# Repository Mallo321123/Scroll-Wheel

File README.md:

# 🖱️ High-Resolution Scroll Wheel

> A large, high-resolution scroll wheel inspired by [Engineer Bo](https://www.patreon.com/c/engineerbo/posts)'s [YouTube video](https://www.youtube.com/watch?v=FSy9G6bNuKA).

---

## [Documentation](https://wiki.mariolanghammer.de/en/Projects/Scroll-Wheel)

---

> ⚠️ **Early Development Phase**  
> This project is still under development. Use at your own risk.

---

## 📅 Roadmap

- [X] BLE HID Support
- [ ] Mouse Wheel Click Functionality
- [ ] Automatic power off
- [ ] Battery Level tuning
- [ ] Enclosure refinements
- [ ] Scroll acceleration modes

---

## 🔧 Hardware Overview

- **Main Controller:** ESP32 (subject to maybe change later)
- **Magnetic Encoder:** [AS5600](https://ams-osram.com/products/sensor-solutions/position-sensors/ams-as5600-position-sensor)
- **Battery Pack:** S3P2 NiMH Eneloop cells

---

## 💻 Software Architecture

The entire functionality is now handled by a single **ESP32 microcontroller** using **BLE HID** (Human Interface Device) mode.

- The scroll wheel inputs are directly interpreted by the ESP32.
- Input data (e.g. rotation) is sent over **Bluetooth Low Energy** as **HID events**, emulating a native scroll device.
- No additional driver or software is needed on the PC — it works like a standard Bluetooth mouse/scroll input.

> ✅ This simplifies the setup significantly and increases compatibility across Linux, Windows, and macOS.

---

## 🧩 Required Components

| Part                             | Quantity |
|----------------------------------|----------|
| Main PCB (pre-soldered)          | 1        |
| Bearing (65×85×10 mm)            | 1        |
| JST GH Cable Kit                 | 1 set    |
| Cylinder Magnets (3×12 mm)       | 7        |
| 3D-Printed Parts                 | 3        |
| S3P2 NiMH Battery Pack           | 1        |
| M2×5 Screws                      | 5        |

---

## 🛠️ Build Guide

### 🔄 Bearing Preparation

Factory bearings may feel stiff due to thick grease. Here's how to optimize smoothness:

1. Remove both sealing rings.
2. Soak the bearing in **isopropyl alcohol** (or another grease remover).
3. Scrub out all remaining grease.
4. Let it dry for ~3 hours.
5. Reinstall **one** sealing ring.
6. Add **light machine oil** generously into the bearing.
7. Reinstall the **second** sealing ring.
8. Spin the bearing multiple times to distribute the oil.
9. *(Optional)* Remove the seals again for an even smoother feel (at the cost of dust protection).

---

## 🚧 Development Gallery

### 🔌 First PCB Prototype (with known bugs)

---

### 🧱 PCB Inside the Case

---

### 🧪 First Firmware Test (External ESP32)

---

### 🧰 Fully Assembled PCB

---

### 🆕 PCB V2 – Improved & Debugged

---

## 🤝 Contributing

Pull requests, suggestions, and feedback are always welcome — feel free to get involved and help improve the project!  
Prototyping and hardware development can get expensive quickly, so if you’d like to support the project financially:

&nbsp;

Every bit helps keep the ideas (and soldering irons) running!

## Credits
Credits to [T-vk](https://github.com/T-vK) for creating the [ESP32 BLE Mouse](https://github.com/T-vK/ESP32-BLE-Mouse) Library

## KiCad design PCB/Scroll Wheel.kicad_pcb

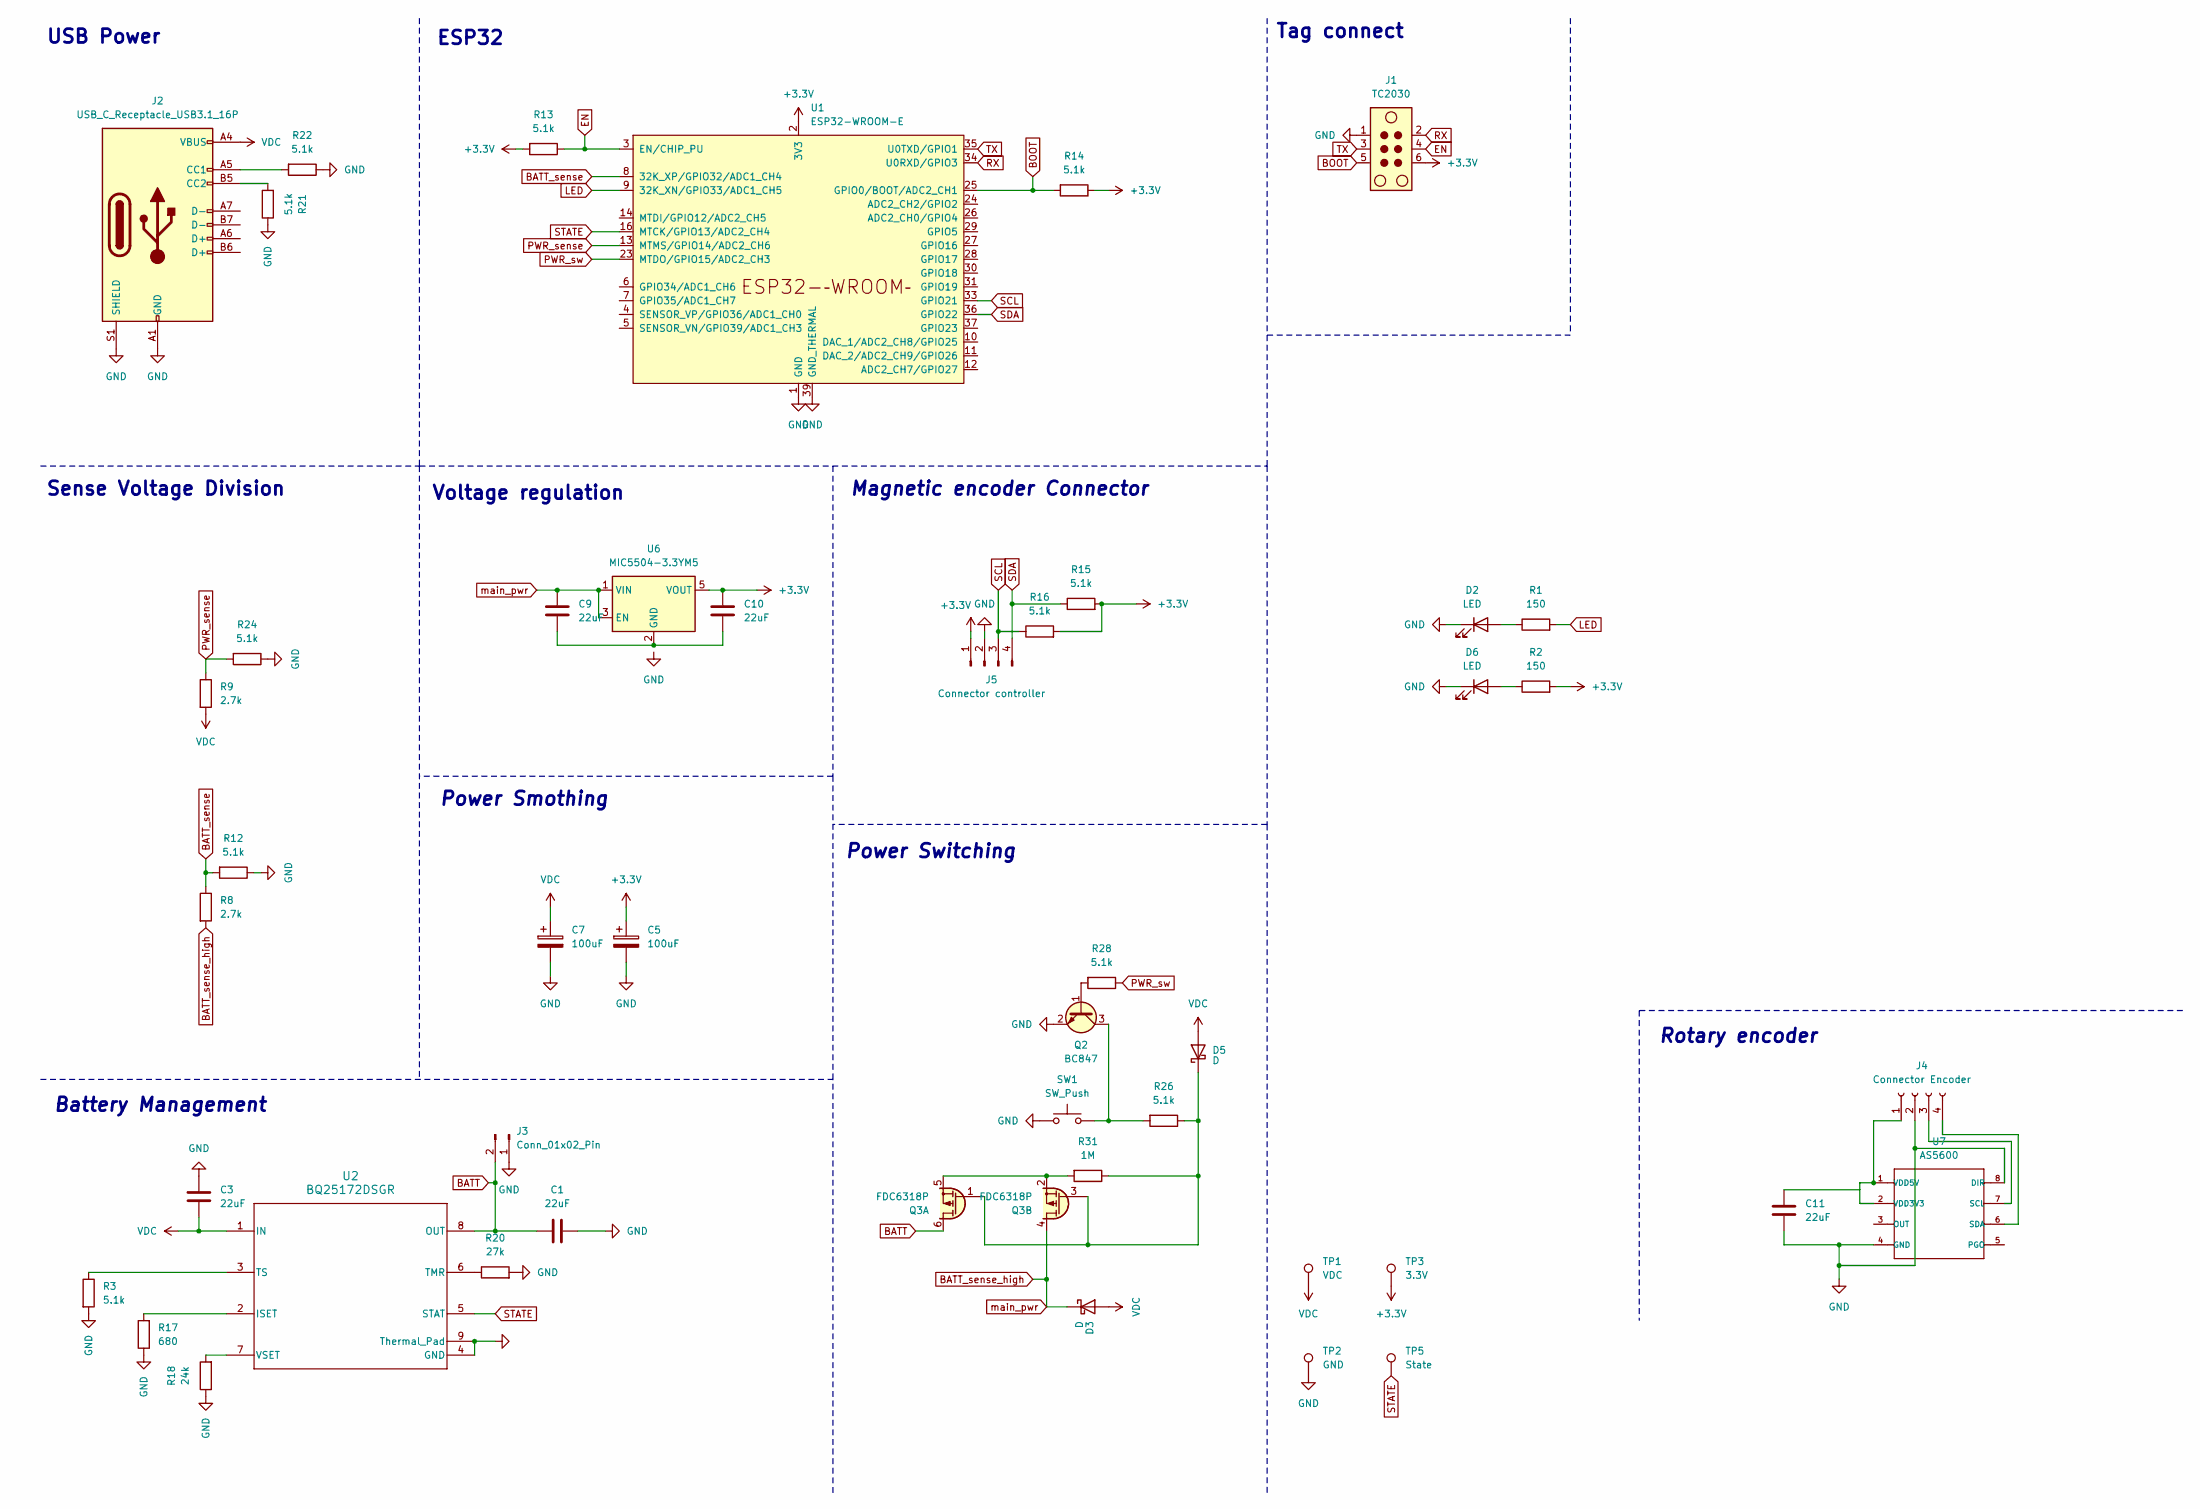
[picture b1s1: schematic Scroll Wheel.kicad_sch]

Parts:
C1, C3, C9, C10, C11: 22uF; C_0402_1005Metric; LCSC C22367823
C5, C7: 100uF; CP_Elec_6.3x5.4; LCSC C72494
D2, D6: LED; D_0402_1005Metric; LCSC C397045
D3, D5: D; D_0402_1005Metric; LCSC C28646385
J1: TC2030; Tag-Connect_TC2030-IDC-NL_2x03_P1.27mm_Vertical
J2: USB_C_Receptacle_USB3.1_16P; USB_C_Receptacle_GCT_USB4110; LCSC C5187472
J3: Conn_01x02_Pin; JST_GH_SM02B-GHS-TB_1x02-1MP_P1.25mm_Horizontal; LCSC C189893
J4: Connector Encoder; JST_GH_SM04B-GHS-TB_1x04-1MP_P1.25mm_Horizontal; LCSC C189895
J5: Connector controller; JST_GH_SM04B-GHS-TB_1x04-1MP_P1.25mm_Horizontal; LCSC C189895
Q2: BC847; SOT-23; LCSC C57668
Q3: FDC6318P; SOT-23-6; LCSC C7472919
R1, R2: 150; R_0402_1005Metric; LCSC C138054
R3, R12, R13, R14, R15, R16, R21, R22, R24, R26, R28: 5.1k; R_0402_1005Metric; LCSC C25905
R8, R9: 2.7k; R_0402_1005Metric; LCSC C138017
R17: 680; R_0402_1005Metric; LCSC C137948
R18: 24k; R_0402_1005Metric; LCSC C2933082
R20: 27k; R_0402_1005Metric; LCSC C138022
R31: 1M; R_0402_1005Metric; LCSC C138033
SW1: SW_Push; SW_Push_SPST_NO_Alps_SKRK; LCSC C720477
TP1: VDC; TestPoint_Pad_D1.0mm
TP2: GND; TestPoint_Pad_D1.0mm
TP3: 3.3V; TestPoint_Pad_D1.0mm
TP5: State; TestPoint_Pad_D1.0mm
U1: ESP32-WROOM-E; ESP32-WROOM-32E; LCSC C701342
U2: BQ25172DSGR; DSG0008A-IPC_A; LCSC C5189434
U6: MIC5504-3.3YM5; SOT-23-5; LCSC C41348078
U7: AS5600; LCSC C499458

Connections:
+3.3V: C5.1, C10.2, J1.6, J5.1, R2.2, R13.2, R14.1, R15.2, R16.2, TP3.1, U1.2 (3V3), U6.5 (VOUT)
BATT: C1.2, J3.2, Q3.6 (D1), U2.8 (OUT)
BATT_sense: R8.1, R12.2, U1.8 (32K_XP/GPIO32/ADC1_CH4)
BATT_sense_high: C9.2, D3.1 (K), Q3.4 (D2), R8.2, U6.1 (VIN), U6.3 (EN)
BOOT: J1.5, R14.2, U1.25 (GPIO0/BOOT/ADC2_CH1)
EN: J1.4, R13.1, U1.3 (EN/CHIP_PU)
GND: C1.1, C3.2, C5.2, C7.2, C11.1, D2.1 (K), D6.1 (K), J1.1, J2.A1 (GND), J2.A12 (GND), J2.B1 (GND), J2.B12 (GND), J2.S1 (SHIELD), J3.1, J3.MP, J4.2, J4.MP, J5.2, J5.MP, Q2.2 (E), R3.2, R12.1, R17.1, R18.1, R20.2, R21.1, R22.1, R24.1, SW1.1, TP2.1, U1.1 (GND), U1.15 (GND), U1.38 (GND), U1.39 (GND_THERMAL), U2.4 (GND), U2.9 (Thermal_Pad), U7.4 (GND), U7.8 (DIR)
LED: R1.2, U1.9 (32K_XN/GPIO33/ADC1_CH5)
unnamed: D2.2 (A), R1.1
unnamed: D5.1 (K), Q3.1 (G1), Q3.3 (G2), R26.1, R31.1
unnamed: D6.2 (A), R2.1
unnamed: J2.A5 (CC1), R22.2
unnamed: J2.B5 (CC2), R21.2
unnamed: C11.2, J4.1, U7.1 (VDD5V), U7.2 (VDD3V3)
unnamed: J4.3, U7.7 (SCL)
unnamed: J4.4, U7.6 (SDA)
unnamed: Q2.1 (B), R28.2
unnamed: Q2.3 (C), R26.2, SW1.2
unnamed: Q3.2 (S2), Q3.5 (S1), R31.2
unnamed: R17.2, U2.2 (ISET)
unnamed: R20.1, U2.6 (TMR)
unnamed: R3.1, U2.3 (TS)
unnamed: R18.2, U2.7 (VSET)
unnamed: C9.1, C10.1, U6.2 (GND)
PWR_sense: R9.1, R24.2, U1.13 (MTMS/GPIO14/ADC2_CH6)
PWR_sw: R28.1, U1.23 (MTDO/GPIO15/ADC2_CH3)
RX: J1.2, U1.34 (U0RXD/GPIO3)
SCL: J5.3, R16.1, U1.33 (GPIO21)
SDA: J5.4, R15.1, U1.36 (GPIO22)
STATE: TP5.1, U1.16 (MTCK/GPIO13/ADC2_CH4), U2.5 (STAT)
TX: J1.3, U1.35 (U0TXD/GPIO1)
VDC: C3.1, C7.1, D3.2 (A), D5.2 (A), J2.A4 (VBUS), J2.A9 (VBUS), J2.B4 (VBUS), J2.B9 (VBUS), R9.2, TP1.1, U2.1 (IN)

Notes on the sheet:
Battery Management
Power Smothing
Magnetic encoder Connector
Rotary encoder
USB Power
ESP32
Power Switching
Sense Voltage Division
Voltage regulation
Tag connect

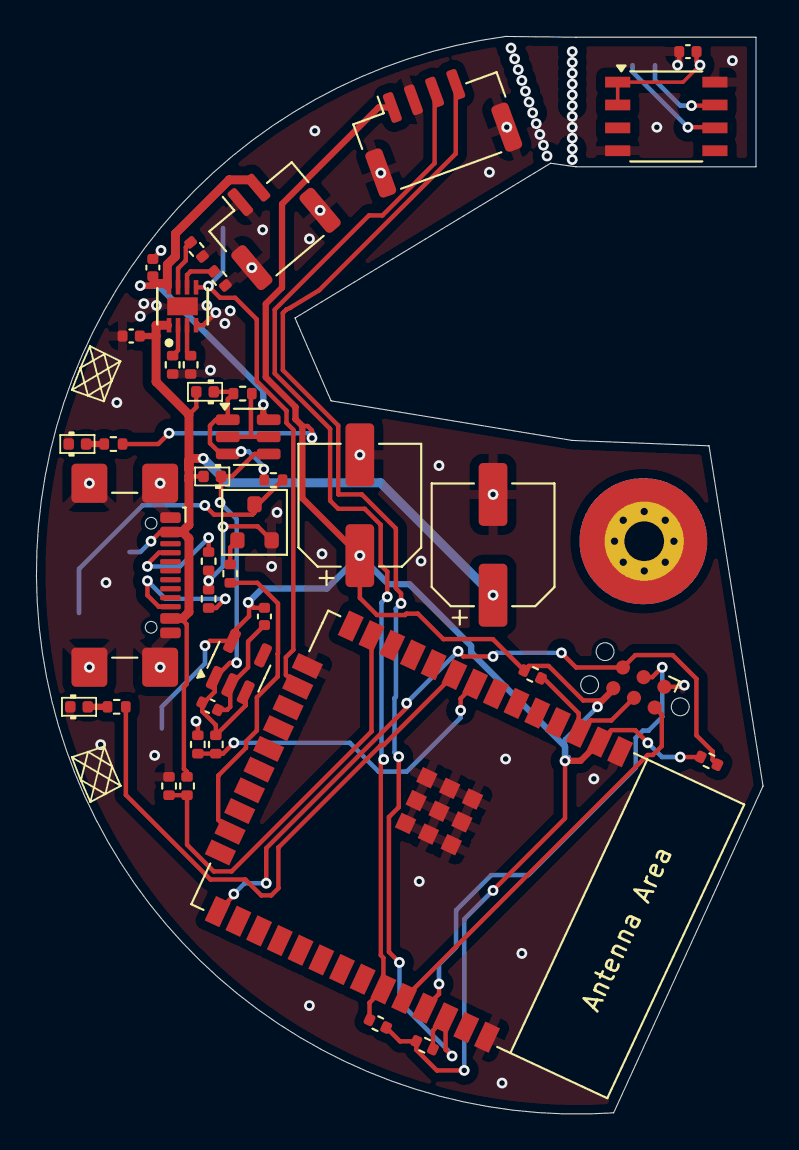
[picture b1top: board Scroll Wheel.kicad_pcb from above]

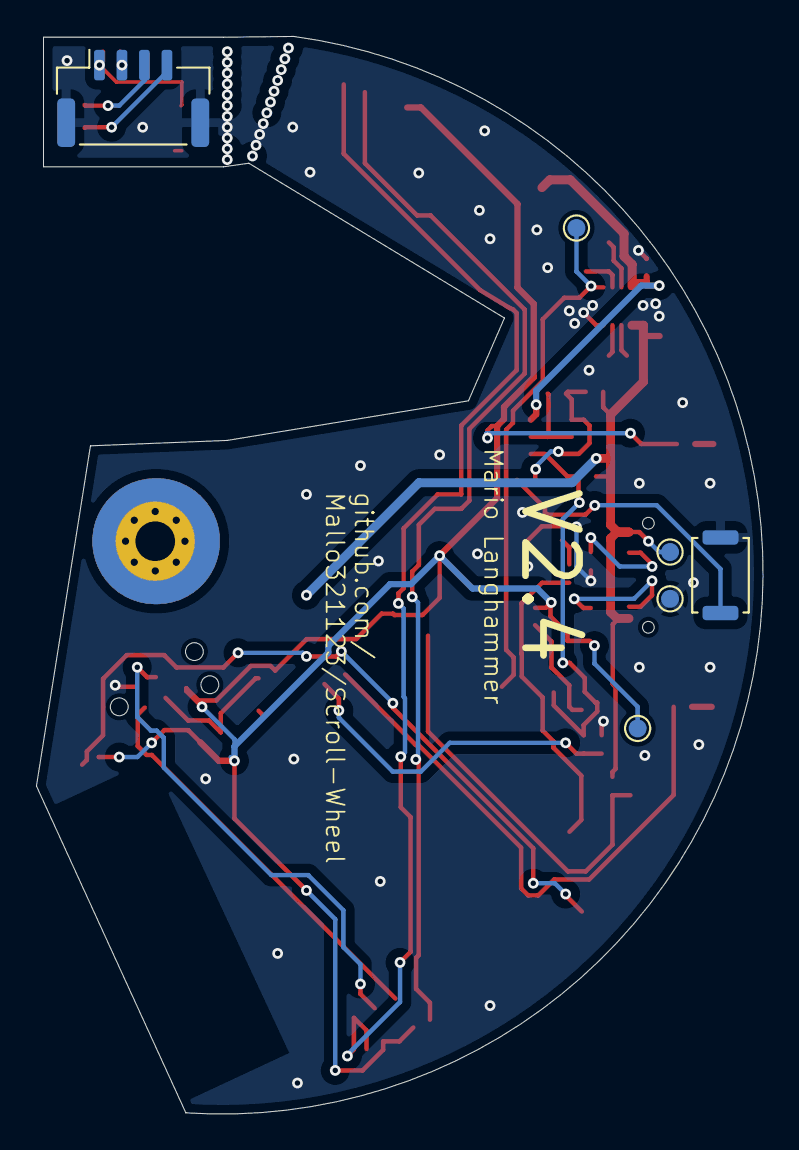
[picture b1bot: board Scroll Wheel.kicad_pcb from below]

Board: 2 copper layers, 40.4 x 59.9 mm, 46 parts (6 on the bottom side), 32 nets.

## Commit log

2025-04-29 Fix Custom Imports
2025-05-01 Battery Part Redesign
2025-05-01 basic cad model
2025-05-05 fix NMOS to PMOS, and 3d Modells
2025-05-08 Fix PCB libs
2025-05-08 Finish CAD Model
2025-05-08 Fix Git fuckup
2025-05-08 add Python driver
2025-05-08 add ESP Firmware
2025-05-08 add missing label
2025-05-08 add vscode directory to gitignore
2025-05-09 esp firmware cleanup
2025-05-10 added AS5600 integration
2025-05-10 add a skirt under the Bearing and tweak some tolerances
2025-05-10 fix to tight tolerances between Bearing and Top
2025-05-10 some code cleanup
2025-05-11 better mounting for Bearing
2025-05-11 replace charge state leds with power and status leds
2025-05-14 Fix #5
2025-05-14 Fix #3 and #4
2025-05-14 Fix #7
2025-05-14 change charge controller caps to known value
2025-05-14 Complete rerouting, fixing all open issues #6 #2 #1
2025-05-20 add better PCB mounting solution in the Case
2025-05-20 some fixing and value tweaking
2025-05-20 add a better mounting solution
2025-06-25 added some Pictures for documentation
2025-06-25 add PCB-rendering image
2025-06-29 some CAD Improvements
2025-06-29 generate new PCB Production files
2025-06-29 Switch from BLE Uart to BLE HID
2025-06-29 code Cleanup
2025-10-22 Add credits section to README
    Added credits section for T-vk and ESP32 BLE Mouse library.
2026-02-07 Add documentation link to README
    Added documentation section link to README.
